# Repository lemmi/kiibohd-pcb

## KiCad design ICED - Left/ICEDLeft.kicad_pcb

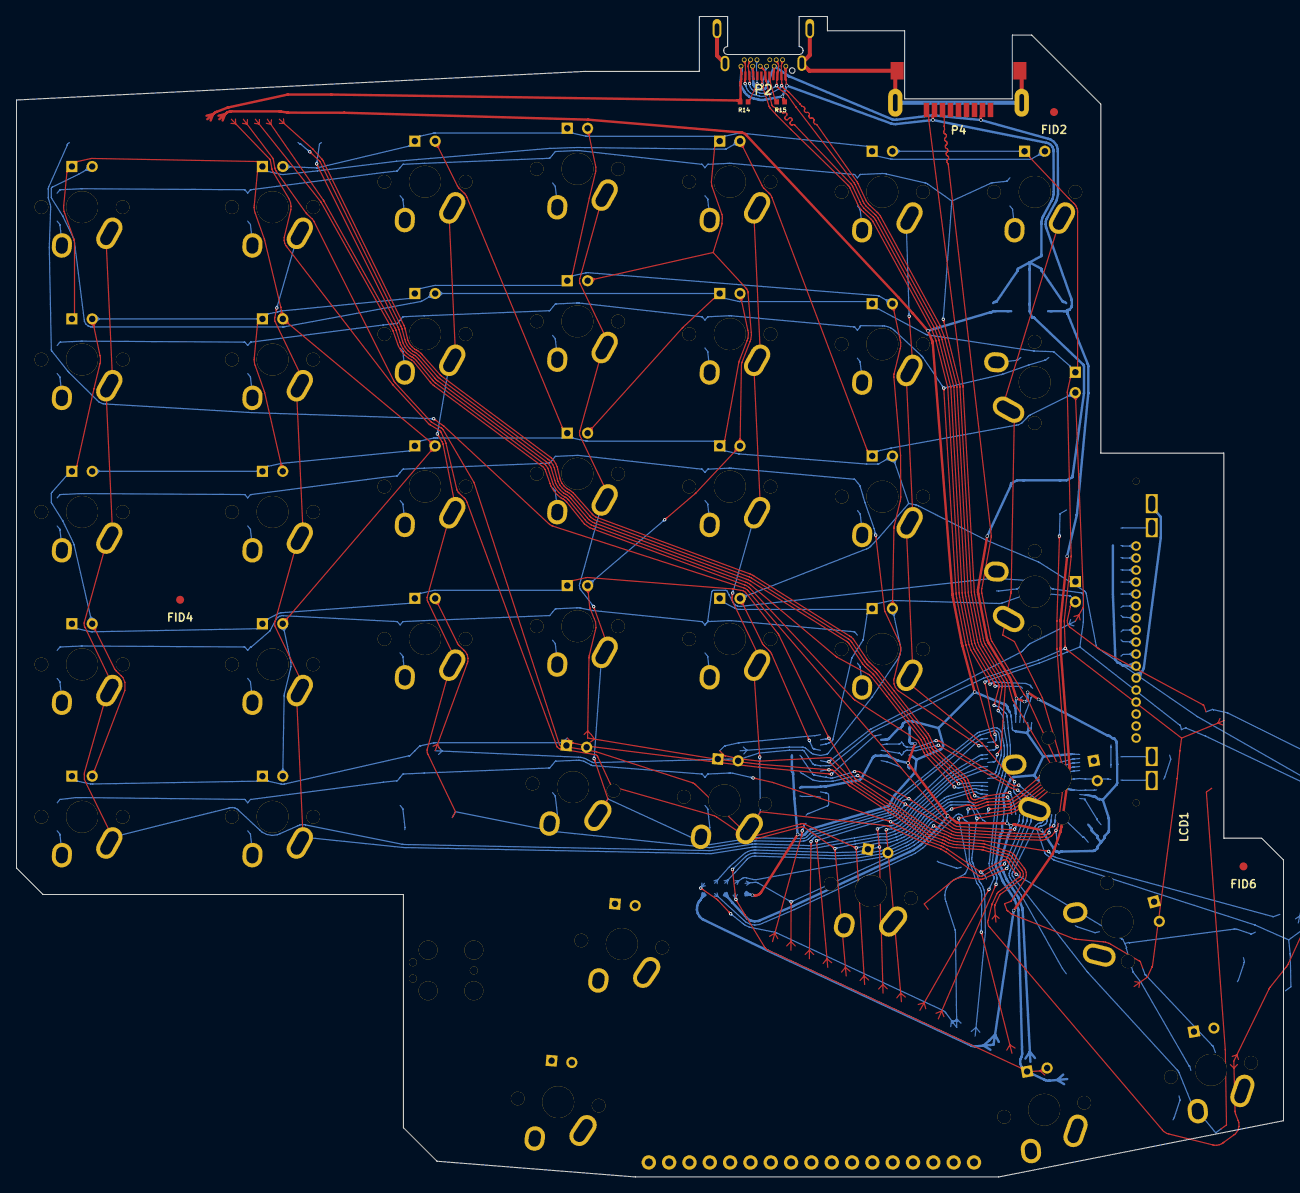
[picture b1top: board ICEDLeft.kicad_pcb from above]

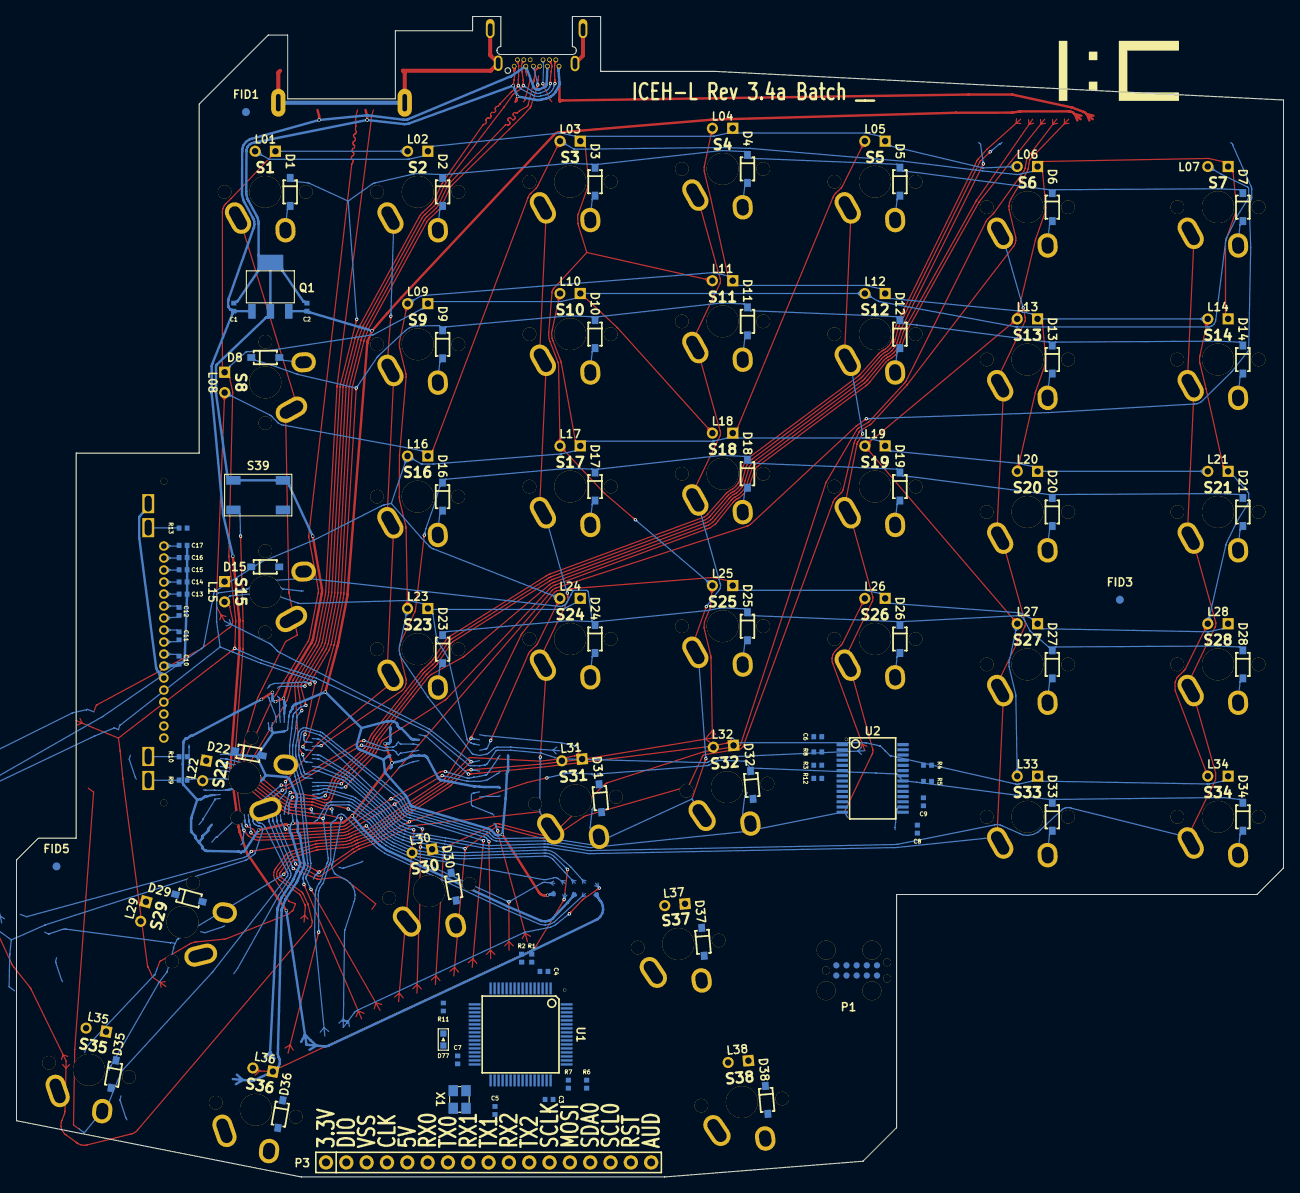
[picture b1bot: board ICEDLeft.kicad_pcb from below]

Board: 2 copper layers, 158.3 x 145.0 mm, 164 parts (80 on the bottom side), 114 nets.

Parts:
C1, C2, C6, C10, C11, C12, C13, C14, C15, C16, C17: 1uF; SMD-1005
C3, C4, C5, C7, C9: 0.1uF; SMD-1005
C8: 0.22uF; SMD-1005
D1, D2, D3, D4, D5, D6, D7, D8, D9, D10, D11, D12, D13, D14, D15, D16, D17, D18, D19, D20, D21, D22, D23, D24, D25, D26, D27, D28, D29, D30, D31, D32, D33, D34, D35, D36, D37, D38: DIODE; SOT123-DIODE
D77: LED; LED-0603
FID1, FID2, FID3, FID4, FID5, FID6: >VALUE; FID
IC_LOGO: IC_LOGO
L01, L02, L03, L04, L05, L06, L07, L08, L09, L10, L11, L12, L13, L14, L15, L16, L17, L18, L19, L20, L21, L22, L23, L24, L25, L26, L27, L28, L29, L30, L31, L32, L33, L34, L35, L36, L37, L38: LED; INSW_LEDS_REG
LCD1: NHD-C12832A1Z
P1: FLASH_HDR; JLINK_NEEDLE
P2: USBC; USB_C_MIDMOUNT_TH_IMPCUT
P3: CONN_17; HEADER_1x17
P4: USB3_AFEMALE; USB3_AFEMALE_MOD
Q1: TC1264; SOT-223
R1, R2, R13: 33; SMD-1005
R3, R4, R5: 4.7k; SMD-1005
R6, R7: 100; SMD-1005
R8: 100k; SMD-1005
R9, R10: 66.5; SMD-1005
R11: 1k; SMD-1005
R12: 20k; SMD-1005
R14, R15: 5.1k; SMD-1005
S1, S2, S3, S4, S5, S6, S7, S8, S9, S10, S11, S12, S13, S14, S15, S16, S17, S18, S19, S20, S21, S22, S23, S24, S25, S26, S27, S28, S29, S30, S31, S32, S33, S34, S35, S36, S37, S38: SW; MXALPS
S39: TAC_SWITCH; TACT_5.2x5.2
U1: MK20DX256VLH7; LQFP64
U2: IS31FL3731C; SSOP-28
X1: CRYSTAL; NX3225SA

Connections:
+5V: C1.1, P1.5, P2.4, P2.9, P2.16, P2.21, P3.5, P4.1, Q1.1
/Col1: S1.1, S8.1, S15.1, S22.1, S29.1, S35.1, U1.37, U1.41
/Col2: S2.1, S9.1, S16.1, S23.1, S30.1, S36.1, U1.38, U1.42
/Col3: S3.1, S10.1, S17.1, S24.1, S31.1, S37.1, U1.43
/Col4: S4.1, S11.1, S18.1, S25.1, S32.1, S38.1, U1.54
/Col5: S5.1, S12.1, S19.1, S26.1, U1.55
/Col6: S6.1, S13.1, S20.1, S27.1, S33.1, U1.56
/Col7: S7.1, S14.1, S21.1, S28.1, S34.1, U1.57
/GND: P2.25, P4.10
/Row1: D1.2, D2.2, D3.2, D4.2, D5.2, D6.2, D7.2, U1.58
/Row2: D8.2, D9.2, D10.2, D11.2, D12.2, D13.2, D14.2, U1.61
/Row3: D15.2, D16.2, D17.2, D18.2, D19.2, D20.2, D21.2, U1.62
/Row4: D22.2, D23.2, D24.2, D25.2, D26.2, D27.2, D28.2, U1.63
/Row5: D29.2, D30.2, D31.2, D32.2, D33.2, D34.2, U1.64
/Row6: D35.2, D36.2, D37.2, D38.2
/ledmatrix/CA1: L01.2, L02.1, L03.1, L04.1, L05.1, L06.2, L11.2, L17.2, L25.2, L29.2, L32.2, L36.2, U2.21
/ledmatrix/CA2: L01.1, L02.2, L07.2, L08.1, L09.1, L10.1, L12.2, L18.2, L22.2, L26.2, L37.2, L38.2, U2.22
/ledmatrix/CA3: L03.2, L06.1, L07.1, L08.2, L13.2, L14.1, L15.2, L16.1, L19.2, L27.2, L30.2, L33.2, U2.23
/ledmatrix/CA4: L04.2, L09.2, L11.1, L12.1, L13.1, L14.2, L20.2, L21.1, L23.2, L28.2, L31.2, L34.2, U2.24
/ledmatrix/CA5: L05.2, L10.2, L16.2, L17.1, L18.1, L19.1, L20.1, L21.2, L24.2, L35.2, U2.25
/ledmatrix/CA6: L15.1, L23.1, L24.1, L29.1, L37.1, U2.26
/ledmatrix/CA7: L25.1, L26.1, L27.1, L28.1, L35.1, U2.27
/ledmatrix/CA8: L22.1, L30.1, L31.1, L36.1, U2.28
/ledmatrix/CA9: L32.1, L33.1, L34.1, L38.1, U2.1
/mcu/A0: LCD1.17, U1.52
/mcu/AUD: C8.2, P3.17
/mcu/INTB: R3.2, U1.40, U2.4
/mcu/LCD_KB: R9.2, U1.46
/mcu/LCD_KG: R10.2, U1.45
/mcu/LCD_KR: R13.2, U1.44
/mcu/MCU_RESET: C5.1, P1.10, P3.16, S39.2, U1.34
/mcu/MOSI: LCD1.15, P3.13, U1.51
/mcu/PTA5: D77.1, P1.9, U1.27
/mcu/RST: LCD1.18, U1.53
/mcu/RX0: P1.8, P3.6, P4.6, U1.23
/mcu/RX1: P2.3, P2.10, P2.15, P2.22, P3.8, U1.2
/mcu/RX2: P3.10, U1.59
/mcu/SCL0: P3.15, R4.2, U1.35, U2.20
/mcu/SCLK: LCD1.16, P3.12, U1.50
/mcu/SDA0: P3.14, R5.2, U1.36, U2.19
/mcu/SDB: R8.2, U1.39, U2.3
/mcu/SS1: LCD1.19, U1.49
/mcu/SWD_CLK: P1.4, P3.4, R6.2
/mcu/SWD_DIO: P1.2, P3.2, R7.2
/mcu/TX0: P1.6, P3.7, P4.5, U1.24
/mcu/TX1: P2.2, P2.11, P2.14, P2.23, P3.9, U1.1
/mcu/TX2: P1.7, P3.11, U1.60
/mcu/USB_DM: P2.7, P2.19, R2.1
/mcu/USB_DP: P2.6, P2.18, R1.1
unnamed: C8.1, U2.17
unnamed: C9.1, U2.16
unnamed: C10.1, LCD1.12
unnamed: C11.1, LCD1.11
unnamed: C11.2, LCD1.10
unnamed: C12.1, LCD1.9
unnamed: C12.2, LCD1.8
unnamed: C13.2, LCD1.7
unnamed: C14.2, LCD1.6
unnamed: C15.2, LCD1.5
unnamed: C16.2, LCD1.4
unnamed: C17.2, LCD1.3
unnamed: D1.1, S1.2
unnamed: D2.1, S2.2
unnamed: D3.1, S3.2
unnamed: D4.1, S4.2
unnamed: D5.1, S5.2
unnamed: D6.1, S6.2
unnamed: D7.1, S7.2
unnamed: D8.1, S8.2
unnamed: D9.1, S9.2
unnamed: D10.1, S10.2
unnamed: D11.1, S11.2
unnamed: D12.1, S12.2
unnamed: D13.1, S13.2
unnamed: D14.1, S14.2
unnamed: D15.1, S15.2
unnamed: D16.1, S16.2
unnamed: D17.1, S17.2
unnamed: D18.1, S18.2
unnamed: D19.1, S19.2
unnamed: D20.1, S20.2
unnamed: D21.1, S21.2
unnamed: D22.1, S22.2
unnamed: D23.1, S23.2
unnamed: D24.1, S24.2
unnamed: D25.1, S25.2
unnamed: D26.1, S26.2
unnamed: D27.1, S27.2
unnamed: D28.1, S28.2
unnamed: D29.1, S29.2
unnamed: D30.1, S30.2
unnamed: D31.1, S31.2
unnamed: D32.1, S32.2
unnamed: D33.1, S33.2
unnamed: D34.1, S34.2
unnamed: D35.1, S35.2
unnamed: D36.1, S36.2
unnamed: D37.1, S37.2
unnamed: D38.1, S38.2
unnamed: D77.2, R11.1
unnamed: LCD1.2, R13.1
unnamed: LCD1.20, R10.1
unnamed: LCD1.21, R9.1
unnamed: P2.5, R15.1
unnamed: P2.17, R14.1
unnamed: R1.2, U1.5
unnamed: R2.2, U1.6
unnamed: R6.1, U1.22
unnamed: R7.1, U1.25
unnamed: R12.1, U2.6
unnamed: U1.32, X1.1
unnamed: U1.33, X1.3
VDD: C2.1, C3.1, C4.1, C6.2, C7.1, LCD1.1, LCD1.14, P1.1, P3.1, Q1.3, R3.1, R4.1, R5.1, U1.3, U1.7, U1.8, U1.21, U1.30, U1.48, U2.2
VSS: C1.2, C2.2, C3.2, C4.2, C5.2, C6.1, C7.2, C9.2, C10.2, C13.1, C14.1, C15.1, C16.1, C17.1, LCD1.13, P1.3, P2.1, P2.12, P2.13, P2.24, P3.3, P4.4, Q1.2, R8.1, R11.2, R12.2, R14.2, R15.2, S39.3, S39.4, U1.4, U1.31, U1.47, U2.5, U2.18, X1.2, X1.4

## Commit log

2017-05-15 version stamped
2017-05-15 version stamp
2017-05-25 added plate and case overlays to DRW-User layer
2017-05-26 set to ignore temporary bakup files
2017-05-26 moved S38
2017-05-28 moved P1, P3, and S36
2017-05-29 Moved S22 and the labesl for P3
2017-06-03 Moved U1, the MPU, and the entourage of resisters and capaciters.
2017-06-03 spreadsheet to calculate component moves
2017-06-06 moved U2 and S33-S35
2017-06-07 Checkpoint, moving S32.
2017-06-10 moved S32
2017-06-10 moved S21
2017-06-11 moved S31
2017-06-12 moved S30
2017-06-12 moved S23
2017-06-12 moved LCD1
2017-06-15 moved a few edge cuts
2017-06-18 more cut line moves
2017-06-18 finished edge cut lines
2017-06-19 moved trace to R13
2017-06-25 moved LCD components R13, C17, and C16
2017-06-26 moved the rest of the LCD resisters and capaciters
2017-06-27 renamed S21 and S22 as the initial switch reorganization step
2017-06-29 renaming switches ahead of moving the nets
2017-07-03 reoredered switch numbering by corrected row and column
2017-07-03 realigned the nets to match the reordered switches
2017-07-04 reorderd the row and column nets
2017-07-04 started moving the switch grid in the .sch files
2017-07-05 Completed movement of switches into row-column grid.
2017-07-06 renamed/renumbered LED
